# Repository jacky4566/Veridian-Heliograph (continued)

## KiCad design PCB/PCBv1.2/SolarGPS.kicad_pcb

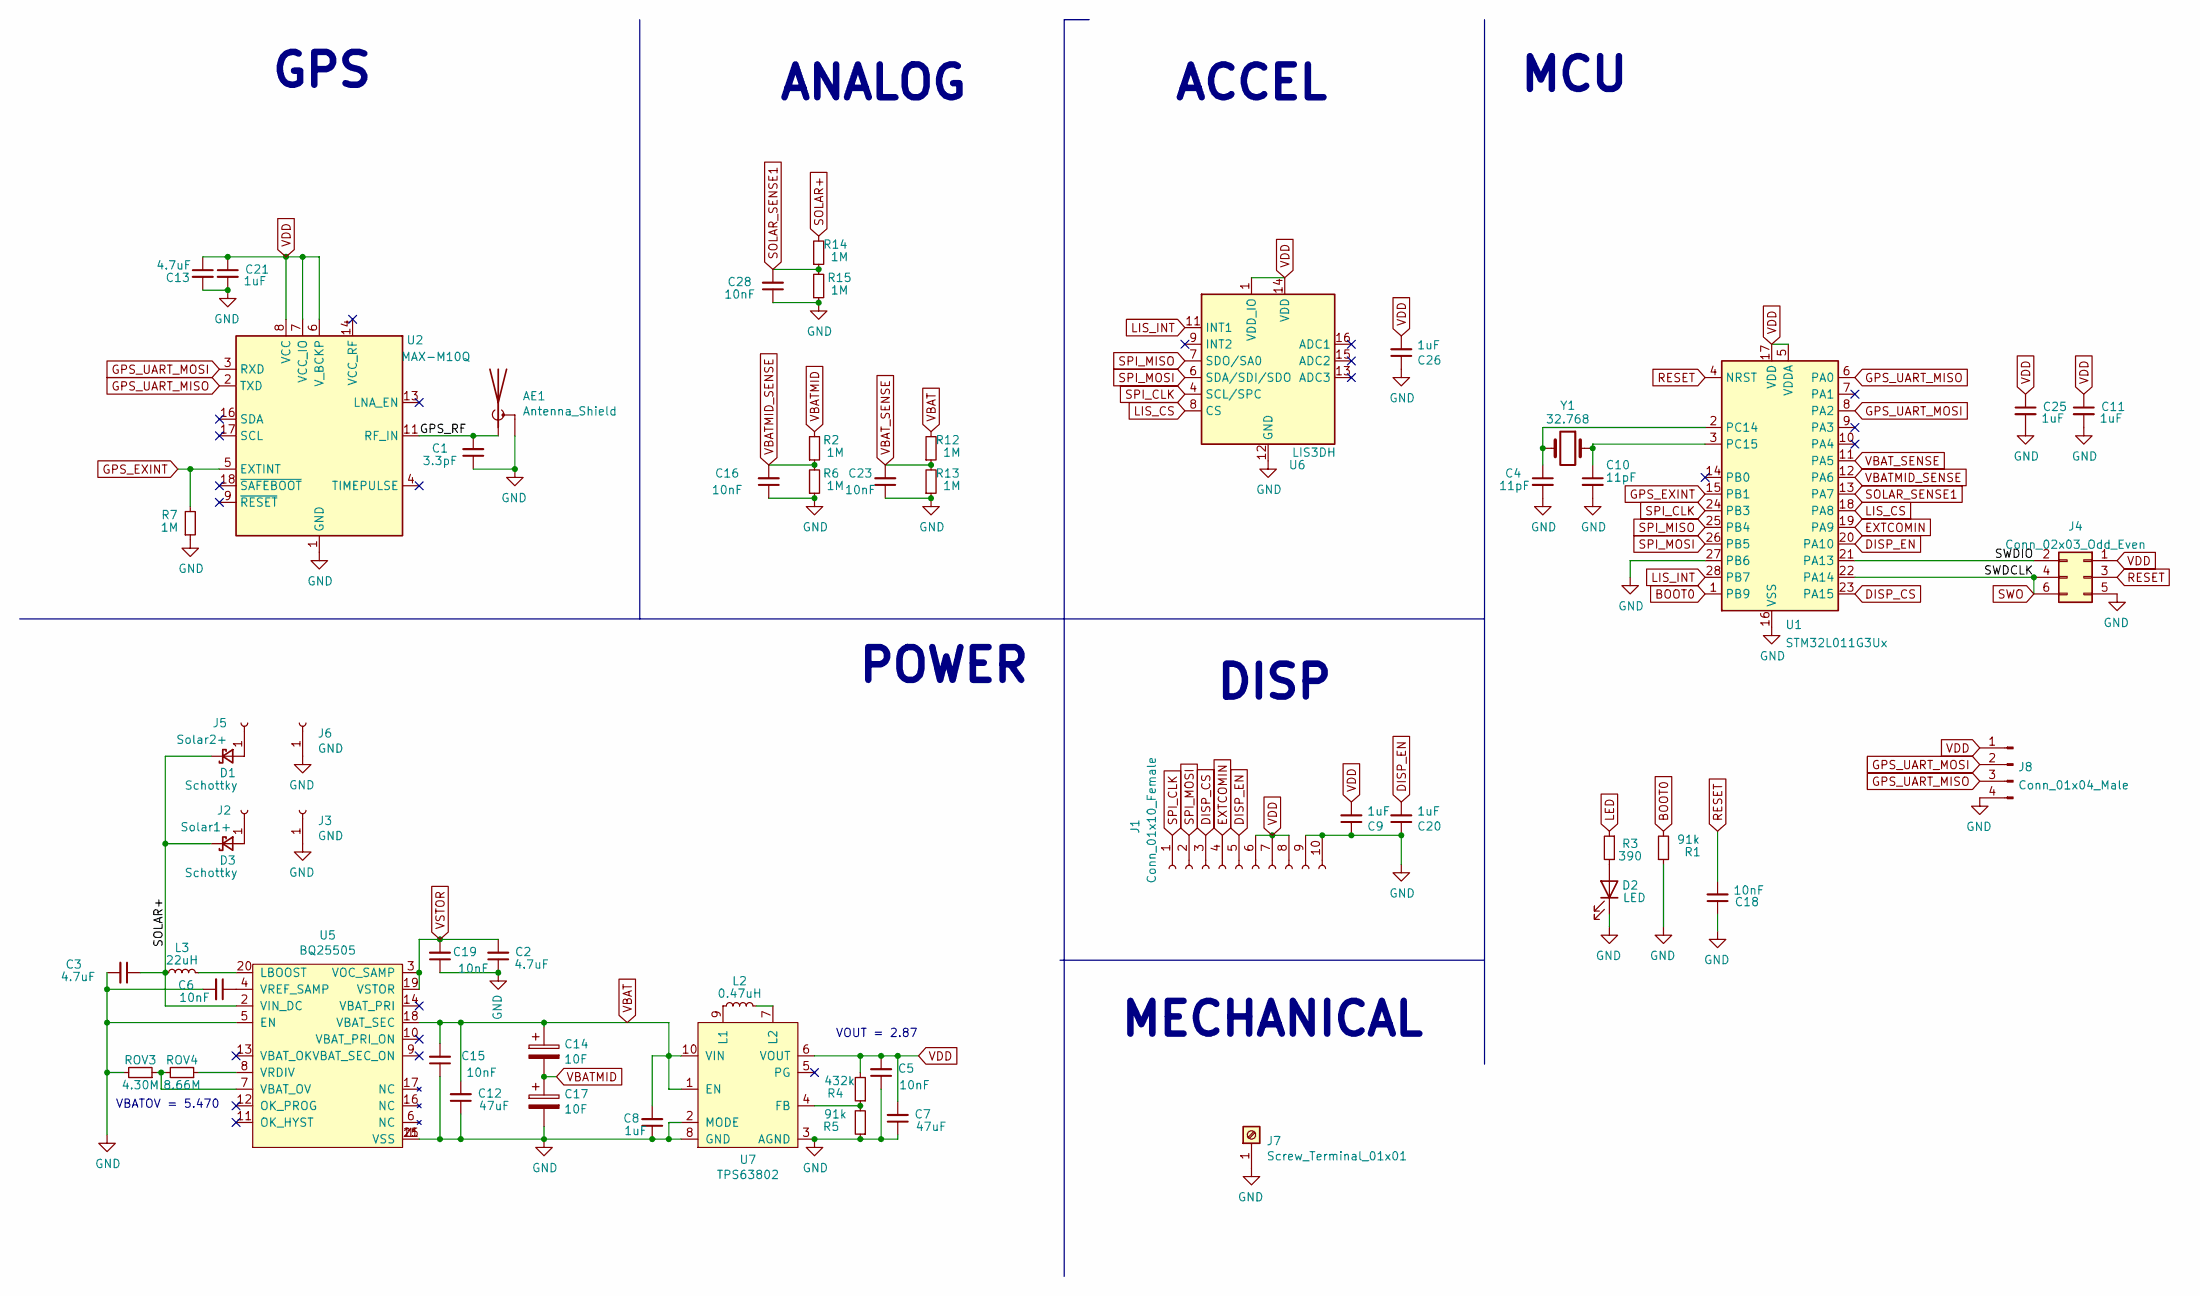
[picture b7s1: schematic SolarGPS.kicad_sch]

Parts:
AE1: Antenna_Shield; Pulse_W3011; Part W3011A
C1: 3.3pF; C_0402_1005Metric
C2, C3, C13: 4.7uF; C_0805_2012Metric
C4, C10: 11pF; C_0603_1608Metric
C5, C6, C15, C16, C18, C19, C23, C28: 10nF; C_0603_1608Metric
C7, C12: 47uF; C_1206_3216Metric
C8, C9, C11, C20, C21, C25, C26: 1uF; C_0603_1608Metric
C14, C17: 10F; SCCT20E106SRB; Part SCCT20E106SRB
D1, D3: Schottky; D_SOD-323_HandSoldering; Part B0530WS
D2: LED; D_0805_2012Metric; Part LS R976-NR-1
J1: Conn_01x10_Female; LS013B7DH03
J2: Solar1+; PinHeader_1x01_P2.54mm_Vertical
J3, J6: GND; PinHeader_1x01_P2.54mm_Vertical
J4: Conn_02x03_Odd_Even; Tag-Connect_TC2030-IDC-NL_2x03_P1.27mm_Vertical
J5: Solar2+; PinHeader_1x01_P2.54mm_Vertical
J7: Screw_Terminal_01x01; M4_RA_7792; Part 7792
J8: Conn_01x04_Male; PinSocket_1x04_P2.54mm_Vertical
L2: 0.47uH; L_0806_2016Metric; Part DFE201612E
L3: 22uH; L_1210_3225Metric; Part CBC3225T220MR
R1, R5: 91k; R_0603_1608Metric
R2, R6, R7, R12, R13, R14, R15: 1M; R_0603_1608Metric
R3: 390; R_0603_1608Metric
R4: 432k; R_0603_1608Metric
ROV3: 4.30M; R_0603_1608Metric
ROV4: 8.66M; R_0603_1608Metric
U1: STM32L011G3Ux; QFN-28_4x4mm_P0.5mm
U2: MAX-M10Q; ublox_MAX
U5: BQ25505; QFN-20-1EP_3.5x3.5mm_P0.5mm_EP2x2mm
U6: LIS3DH; LGA-16_3x3mm_P0.5mm_LayoutBorder3x5y
U7: TPS63802; VREG_TPS63802DLAR
Y1: 32.768; Crystal_SMD_3215-2Pin_3.2x1.5mm; Part SC32S-7PF20PPM

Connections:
/GPS_RF: AE1.1 (A), C1.2, U2.11 (RF_IN)
/SWDIO: J4.2, U1.21 (PA13)
BOOT0: R1.2, U1.1 (PB9)
DISP_CS: J1.3, U1.23 (PA15)
DISP_EN: C20.2, J1.5, U1.20 (PA10)
EXTCOMIN: J1.4, U1.19 (PA9)
GND: AE1.2 (Shield), C1.1, C2.1, C3.2, C4.2, C5.1, C6.2, C7.1, C8.1, C9.1, C10.2, C11.2, C12.1, C13.2, C15.1, C16.1, C17.2, C18.1, C19.1, C20.1, C21.2, C23.1, C25.2, C26.1, C28.1, D2.1 (K), J1.9, J1.10, J3.1, J4.5, J6.1, J7.1, J8.4, R1.1, R5.1, R6.1, R7.1, R13.1, R15.1, ROV3.2, U1.16 (VSS), U1.27 (PB6), U2.1 (GND), U2.10 (GND), U2.12 (GND), U5.1 (VSS), U5.5 (EN), U5.15 (VSS), U5.21 (VSS), U6.5 (GND), U6.10 (GND), U6.12 (GND), U7.2 (MODE), U7.3 (AGND), U7.8 (GND)
GPS_EXINT: R7.2, U1.15 (PB1), U2.5 (EXTINT)
GPS_UART_MISO: J8.3, U1.6 (PA0), U2.2 (TXD)
GPS_UART_MOSI: J8.2, U1.8 (PA2), U2.3 (RXD)
LED: R3.1
LIS_CS: U1.18 (PA8), U6.8 (CS)
LIS_INT: U1.28 (PB7), U6.11 (INT1)
unnamed: C4.1, U1.2 (PC14), Y1.2
unnamed: C6.1, U5.4 (VREF_SAMP)
unnamed: C10.1, U1.3 (PC15), Y1.1
unnamed: D1.2 (A), J5.1
unnamed: D2.2 (A), R3.2
unnamed: D3.2 (A), J2.1
unnamed: L2.1, U7.9 (L1)
unnamed: L2.2, U7.7 (L2)
unnamed: L3.2, U5.20 (LBOOST)
unnamed: R4.1, R5.2, U7.4 (FB)
unnamed: ROV3.1, ROV4.2, U5.7 (VBAT_OV)
unnamed: ROV4.1, U5.8 (VRDIV)
RESET: C18.2, J4.3, U1.4 (NRST)
SOLAR+: C3.1, D1.1 (K), D3.1 (K), L3.1, R14.2, U5.2 (VIN_DC)
SOLAR_SENSE1: C28.2, R14.1, R15.2, U1.13 (PA7)
SPI_CLK: J1.1, U1.24 (PB3), U6.4 (SCL/SPC)
SPI_MISO: U1.25 (PB4), U6.7 (SDO/SA0)
SPI_MOSI: J1.2, U1.26 (PB5), U6.6 (SDA/SDI/SDO)
SWO: J4.4, J4.6, U1.22 (PA14)
VBAT: C8.2, C12.2, C14.1, C15.2, R12.2, U5.18 (VBAT_SEC), U7.1 (EN), U7.10 (VIN)
VBATMID: C14.2, C17.1, R2.2
VBATMID_SENSE: C16.2, R2.1, R6.2, U1.12 (PA6)
VBAT_SENSE: C23.2, R12.1, R13.2, U1.11 (PA5)
VDD: C5.2, C7.2, C9.2, C11.1, C13.1, C21.1, C25.1, C26.2, J1.6, J1.7, J1.8, J4.1, J8.1, R4.2, U1.5 (VDDA), U1.17 (VDD), U2.6 (V_BCKP), U2.7 (VCC_IO), U2.8 (VCC), U6.1 (VDD_IO), U6.14 (VDD), U7.6 (VOUT)
VSTOR: C2.2, C19.2, U5.3 (VOC_SAMP), U5.19 (VSTOR)

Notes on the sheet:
VOUT = 2.87
GPS
MCU
ACCEL
DISP
POWER
VBATOV = 5.470
ANALOG
MECHANICAL

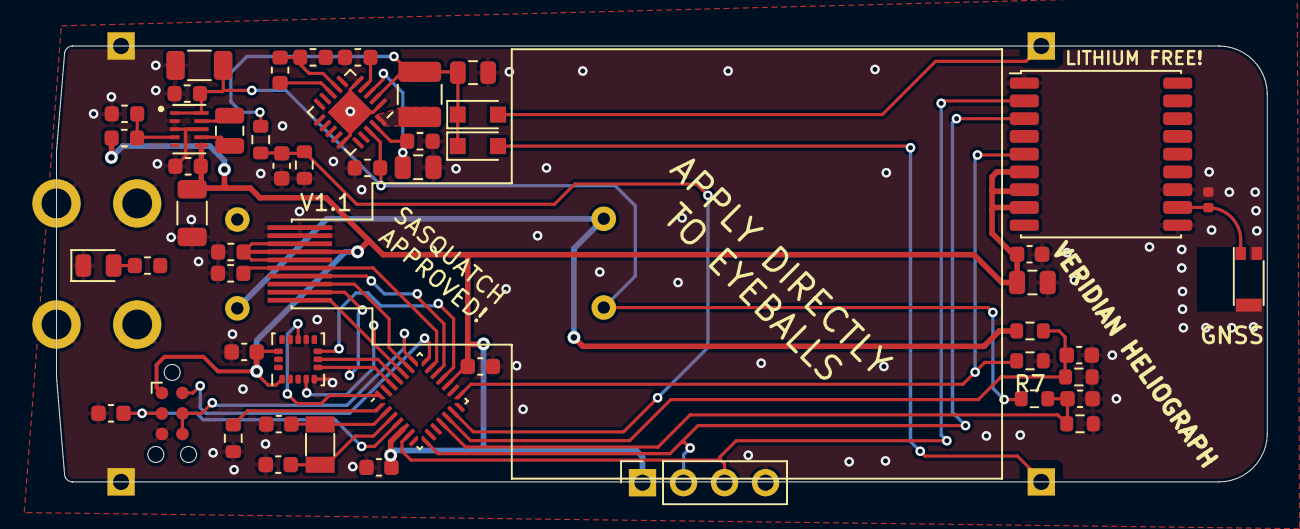
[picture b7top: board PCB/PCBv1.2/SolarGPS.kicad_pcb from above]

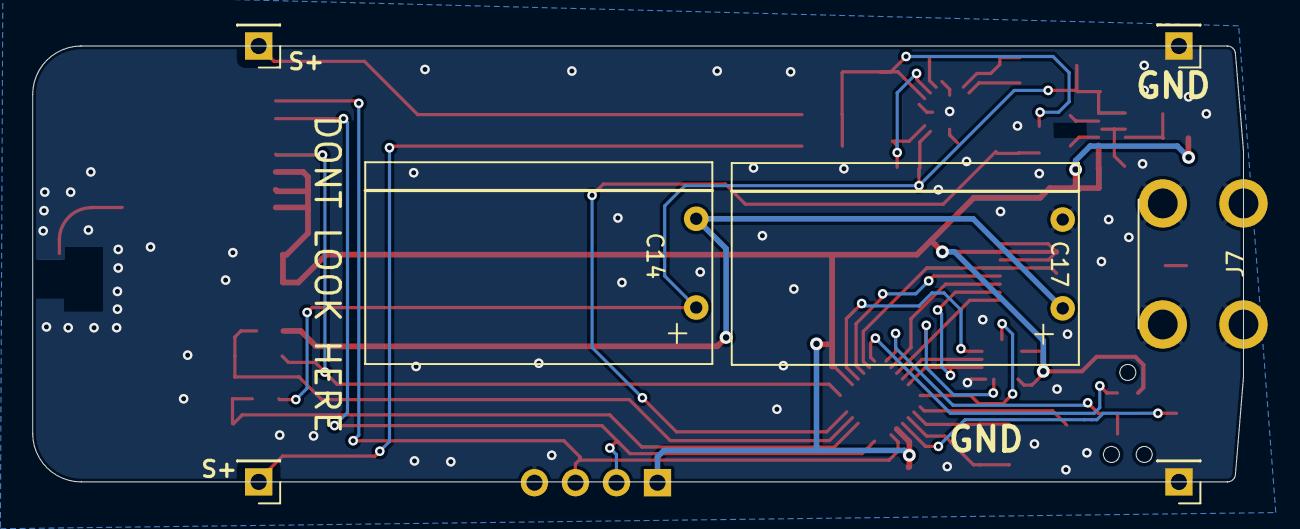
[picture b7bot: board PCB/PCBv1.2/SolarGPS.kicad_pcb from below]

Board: 2 copper layers, 75.0 x 27.0 mm, 58 parts (7 on the bottom side), 37 nets.

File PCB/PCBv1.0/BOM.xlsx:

Reference | Quantity | Value | Footprint | MANUFACTURER Part | Manufacture | Digikey Part | Cost CAD @100
U4 | 1 | STM32WB5MMGH6TR | Veridian-Library-KiCad:XCVR_STM32WB5MMGH6TR | STM32WB5MMGH6TR | STMicroelectronics | 497-STM32WB5MMGH6CT-ND | 15.1318
U2 | 1 | MAX-M10Q | RF_GPS:ublox_MAX | MAX-M10M-00B | U-Blox | 672-MAX-M10M-00BCT-ND | 12.2097
U5 | 1 | BQ25505 | Package_DFN_QFN:QFN-20-1EP_3.5x3.5mm_P0.5mm_EP2x2mm_ThermalVias | BQ25505RGRR | Texas Instruments | 296-37078-1-ND | 5.0499000000000001
C14 C17 | 2 | 10F | Veridian-Library-KiCad:SCCT20E106SRB | SCCT20E106SRB | KYOCERA AVX | 478-11288-ND | 2.9862000000000002
U6 | 1 | LIS3DH | Package_LGA:LGA-16_3x3mm_P0.5mm_LayoutBorder3x5y | LIS3DHTR | STMicroelectronics | 497-10613-1-ND | 2.0329999999999999
U7 | 1 | TPS63802 | Margo_Lib:VREG_TPS63802DLAR | TPS63802DLAR | Texas Instruments | 296-TPS63802DLARCT-ND | 1.9172
AE1 | 1 | Antenna_Shield |  | W3011A | PulseLarsen Antennas | 553-1671-1-ND | 1.6272
J1 | 1 | Conn_01x10_Female | Margo_Lib:AYF531035 | AYF531035A | Panasonic Electric Works | 255-5667-ND | 1.0860000000000001
J4 | 1 | Conn_02x05_Odd_Even |  | PM20C05VBDN | METZ CONNECT USA Inc. | 1849-1015-ND | 0.63029999999999997
J7 | 1 | Screw_Terminal_01x01 | Veridian-Library-KiCad:Right Angle Screw Terminal M3M4 | 7781 | Keystone Electronics | 36-7781-ND | 0.5131
C7 C12 | 2 | 100uF | Capacitor_SMD:C_1206_3216Metric | GRM31CD80J107MEA8K | Murata Electronics | 490-GRM31CD80J107MEA8KCT-ND | 0.35210000000000002
L2 | 1 | 0.47uH | Inductor_SMD:L_0806_2016Metric | DFE201612E | Murata Electronics | 490-16593-1-ND | 0.31069999999999998
L3 | 1 | 22uH | Inductor_SMD:L_1008_2520Metric | CBC3225T220MR | Taiyo Yuden | 587-1626-1-ND | 0.27110000000000001
D1 D3 | 2 | Schottky | Diode_SMD:D_SOD-323_HandSoldering | B0530WS | Taiwan Semiconductor Corporation | B0530WSRRGCT-ND | 0.22270000000000001
C2 C3 | 2 | 4.7uF | Capacitor_SMD:C_0805_2012Metric | GRM188Z71A475ME15D | Murata Electronics | 490-GRM188Z71A475ME15DCT-ND | 0.18279999999999999
D4 | 1 | 5.1V | Diode_SMD:D_SOD-523 | BZT52C5V1T-TP | Micro Commercial Co | BZT52C5V1T-TPMSCT-ND | 0.17299999999999999
D2 | 1 | LED | Diode_SMD:D_0805_2012Metric | LS R976-NR-1 | OSRAM Opto Semiconductors Inc. | 475-1278-1-ND | 0.1069
C5 C6 C15 C16 C18 C19 C23 C28 | 8 | 10nF | Capacitor_SMD:C_0603_1608Metric | GRM1885C1H103JA01J | Murata Electronics | 490-GRM1885C1H103JA01JCT-ND | 9.4100000000000003E-2
C1, C10, C11, C13 | 4 | 3.3pF | Capacitor_SMD:C_0402_1005Metric | CBR04C339C5GAC | KEMET | 399-6165-1-ND | 0.06
C4, C8, C9, C20, C21, C25, C26 | 7 | 1uF | Capacitor_SMD:C_0603_1608Metric | GRM188R61A105KA61J | Murata Electronics | 490-6408-1-ND | 3.8899999999999997E-2
R1 R2 R6 R12 R13 R14 R15 | 7 | 1M | Resistor_SMD:R_0603_1608Metric | RC0603FR-071ML | YAGEO | 311-1.00MHRCT-ND | 1.43E-2
R4 | 1 | 412k | Resistor_SMD:R_0603_1608Metric | RC0603FR-07412KL | YAGEO | 311-412KHRCT-ND | 1.43E-2
R5 | 1 | 91k | Resistor_SMD:R_0603_1608Metric | RC0603FR-0791KL | YAGEO | 311-91.0KHRCT-ND | 1.43E-2
ROV3 | 1 | 4.32M | Resistor_SMD:R_0603_1608Metric | RC0603FR-074M3L | YAGEO | 13-RC0603FR-074M3LCT-ND | 1.43E-2
ROV4 | 1 | 8.66M | Resistor_SMD:R_0603_1608Metric | RC0603FR-078M66L | YAGEO | RC0603FR-078M66L-ND | 1.43E-2
R3 | 1 | 390 | Resistor_SMD:R_0603_1608Metric | RC0603JR-07390RL | YAGEO | 311-390GRCT-ND | 1.18E-2
J2 | 1 | Solar1+ |  | DNF
J3 J6 | 2 | GND |  | DNF
J5 | 1 | Solar2+ |  | DNF
DISP1 | 1 |  |  | LS013B7DH03 | Sharp Microelectronics | 425-2903-ND | 11.003
SOLAR | 2 |  |  | SM141K09L | ANYSOLAR Ltd | SM141K09L-ND | 8.5571000000000002
PCB | 1 |  |  |  |  |  | 1
Epoxy | 1 |  |  |  |  |  | 3
 |  |  |  |  |  |  | 82.0989

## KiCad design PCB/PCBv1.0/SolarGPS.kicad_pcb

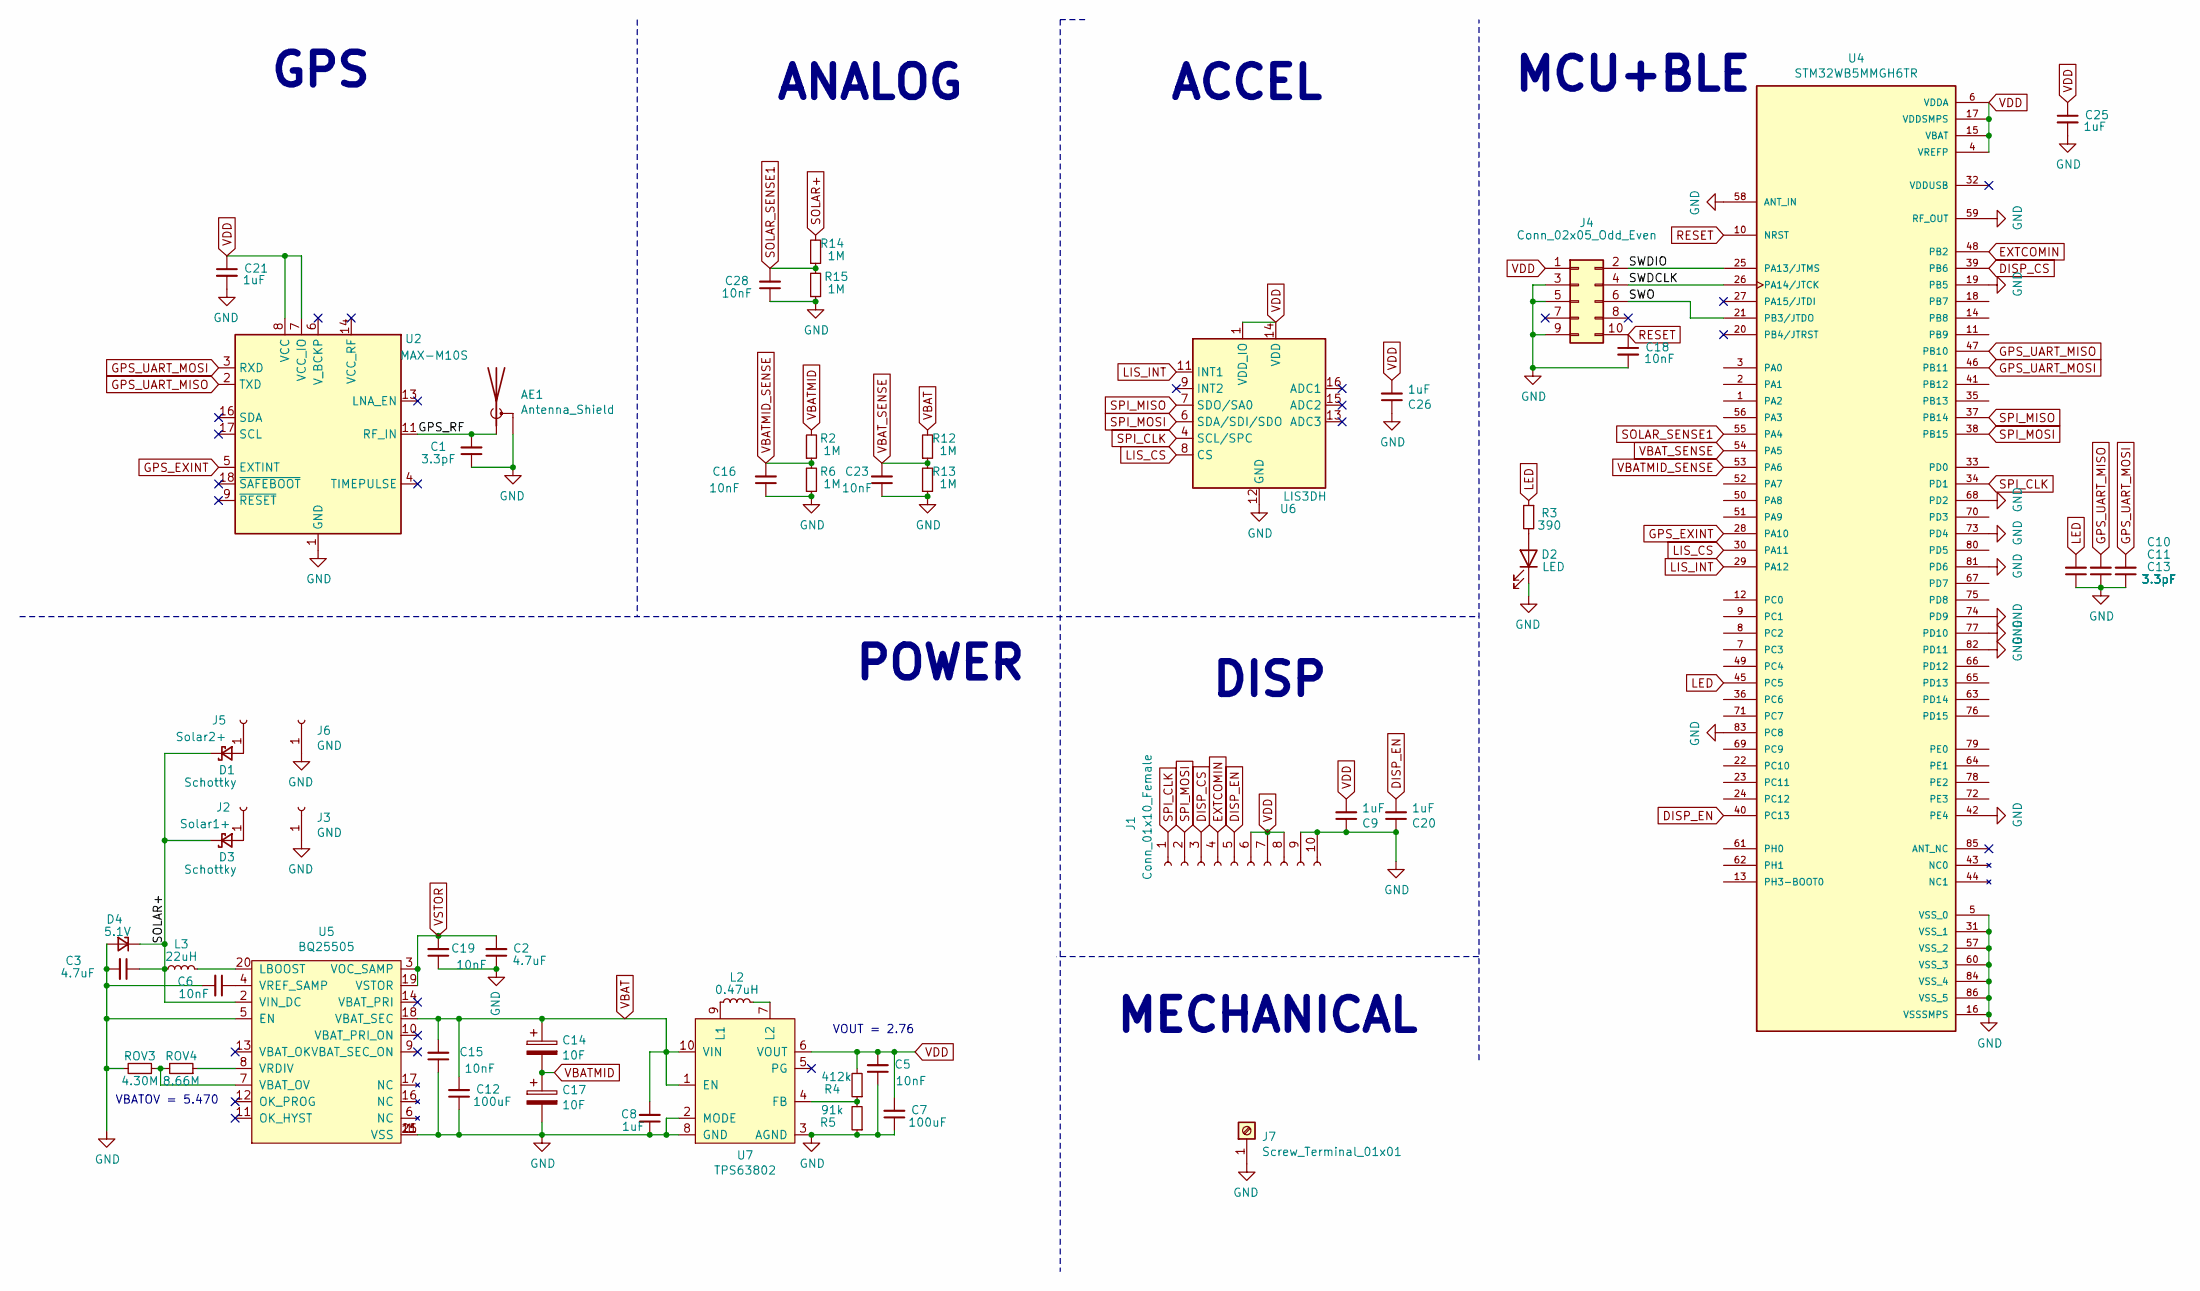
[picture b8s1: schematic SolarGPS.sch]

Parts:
AE1: Antenna_Shield; Pulse_W3011; Part W3011A
C1, C10, C11, C13: 3.3pF; C_0402_1005Metric
C2, C3: 4.7uF; C_0805_2012Metric
C5, C6, C15, C16, C18, C19, C23, C28: 10nF; C_0603_1608Metric
C7, C12: 100uF; C_1206_3216Metric
C8, C9, C20, C21, C25, C26: 1uF; C_0603_1608Metric
C14, C17: 10F; SCCT20E106SRB; Part SCCT20E106SRB
D1, D3: Schottky; D_SOD-323_HandSoldering; Part B0530WS-TP
D2: LED; D_0805_2012Metric; Part LS R976-NR-1
D4: 5.1V; D_SOD-523; Part BZT52C5V1T-TP
J1: Conn_01x10_Female; AYF531035
J2: Solar1+; PinHeader_1x01_P2.54mm_Vertical
J3, J6: GND; PinHeader_1x01_P2.54mm_Vertical
J4: Conn_02x05_Odd_Even; PinHeader_2x05_P2.00mm_Vertical_SMD; Part PM20C05VBDN
J5: Solar2+; PinHeader_1x01_P2.54mm_Vertical
J7: Screw_Terminal_01x01; Right Angle Screw Terminal M3M4; Part 7781
L2: 0.47uH; L_0806_2016Metric; Part CIGT201208EHR47MNE
L3: 22uH; L_1210_3225Metric; Part CBC3225T220MR
R2, R6, R12, R13, R14, R15: 1M; R_0603_1608Metric
R3: 390; R_0603_1608Metric
R4: 412k; R_0603_1608Metric
R5: 91k; R_0603_1608Metric
ROV3: 4.30M; R_0603_1608Metric
ROV4: 8.66M; R_0603_1608Metric
U2: MAX-M10S; ublox_MAX
U4: STM32WB5MMGH6TR; XCVR_STM32WB5MMGH6TR; PARTREV Rev 1
U5: BQ25505; QFN-20-1EP_3.5x3.5mm_P0.5mm_EP2x2mm_ThermalVias
U6: LIS3DH; LGA-16_3x3mm_P0.5mm_LayoutBorder3x5y
U7: TPS63802; VREG_TPS63802DLAR

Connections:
/GPS_RF: AE1.1 (A), C1.2, U2.11 (RF_IN)
/SWDCLK: J4.4, U4.26 (PA14/JTCK)
/SWDIO: J4.2, U4.25 (PA13/JTMS)
/SWO: J4.6, U4.21 (PB3/JTDO)
DISP_CS: J1.3, U4.39 (PB6)
DISP_EN: C20.2, J1.5, U4.40 (PC13)
EXTCOMIN: J1.4, U4.48 (PB2)
GND: AE1.2 (Shield), C1.1, C2.1, C3.2, C5.1, C6.2, C7.1, C8.1, C9.1, C10.1, C11.1, C12.1, C13.1, C15.1, C16.1, C17.2, C18.2, C19.1, C20.1, C21.2, C23.1, C25.2, C26.1, C28.1, D2.1 (K), D4.2 (A), J1.9, J1.10, J3.1, J4.3, J4.5, J4.9, J6.1, J7.1, R5.1, R6.1, R13.1, R15.1, ROV3.2, U2.1 (GND), U2.10 (GND), U2.12 (GND), U4.5 (VSS_0), U4.16 (VSSSMPS), U4.19 (PB5), U4.31 (VSS_1), U4.42 (PE4), U4.57 (VSS_2), U4.58 (ANT_IN), U4.59 (RF_OUT), U4.60 (VSS_3), U4.68 (PD2), U4.73 (PD4), U4.74 (PD9), U4.77 (PD10), U4.81 (PD6), U4.82 (PD11), U4.83 (PC8), U4.84 (VSS_4), U4.86 (VSS_5), U5.1 (VSS), U5.5 (EN), U5.15 (VSS), U5.21 (VSS), U6.5 (GND), U6.10 (GND), U6.12 (GND), U7.2 (MODE), U7.3 (AGND), U7.8 (GND)
GPS_EXINT: U2.5 (EXTINT), U4.28 (PA10)
GPS_UART_MISO: C11.2, U2.2 (TXD), U4.47 (PB10)
GPS_UART_MOSI: C13.2, U2.3 (RXD), U4.46 (PB11)
LED: C10.2, R3.1, U4.45 (PC5)
LIS_CS: U4.30 (PA11), U6.8 (CS)
LIS_INT: U4.29 (PA12), U6.11 (INT1)
unnamed: C6.1, U5.4 (VREF_SAMP)
unnamed: D1.2 (A), J5.1
unnamed: D2.2 (A), R3.2
unnamed: D3.2 (A), J2.1
unnamed: L2.1, U7.9 (L1)
unnamed: L2.2, U7.7 (L2)
unnamed: L3.2, U5.20 (LBOOST)
unnamed: R4.1, R5.2, U7.4 (FB)
unnamed: ROV3.1, ROV4.2, U5.7 (VBAT_OV)
unnamed: ROV4.1, U5.8 (VRDIV)
RESET: C18.1, J4.10, U4.10 (NRST)
SOLAR+: C3.1, D1.1 (K), D3.1 (K), D4.1 (K), L3.1, R14.2, U5.2 (VIN_DC)
SOLAR_SENSE1: C28.2, R14.1, R15.2, U4.55 (PA4)
SPI_CLK: J1.1, U4.34 (PD1), U6.4 (SCL/SPC)
SPI_MISO: U4.37 (PB14), U6.7 (SDO/SA0)
SPI_MOSI: J1.2, U4.38 (PB15), U6.6 (SDA/SDI/SDO)
VBAT: C8.2, C12.2, C14.1, C15.2, R12.2, U5.18 (VBAT_SEC), U7.1 (EN), U7.10 (VIN)
VBATMID: C14.2, C17.1, R2.2
VBATMID_SENSE: C16.2, R2.1, R6.2, U4.53 (PA6)
VBAT_SENSE: C23.2, R12.1, R13.2, U4.54 (PA5)
VDD: C5.2, C7.2, C9.2, C21.1, C25.1, C26.2, J1.6, J1.7, J1.8, J4.1, R4.2, U2.7 (VCC_IO), U2.8 (VCC), U4.4 (VREFP), U4.6 (VDDA), U4.15 (VBAT), U4.17 (VDDSMPS), U6.1 (VDD_IO), U6.14 (VDD), U7.6 (VOUT)
VSTOR: C2.2, C19.2, U5.3 (VOC_SAMP), U5.19 (VSTOR)

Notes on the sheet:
VBATOV = 5.470
VOUT = 2.76
MCU+BLE
POWER
ACCEL
ANALOG
GPS
DISP
MECHANICAL

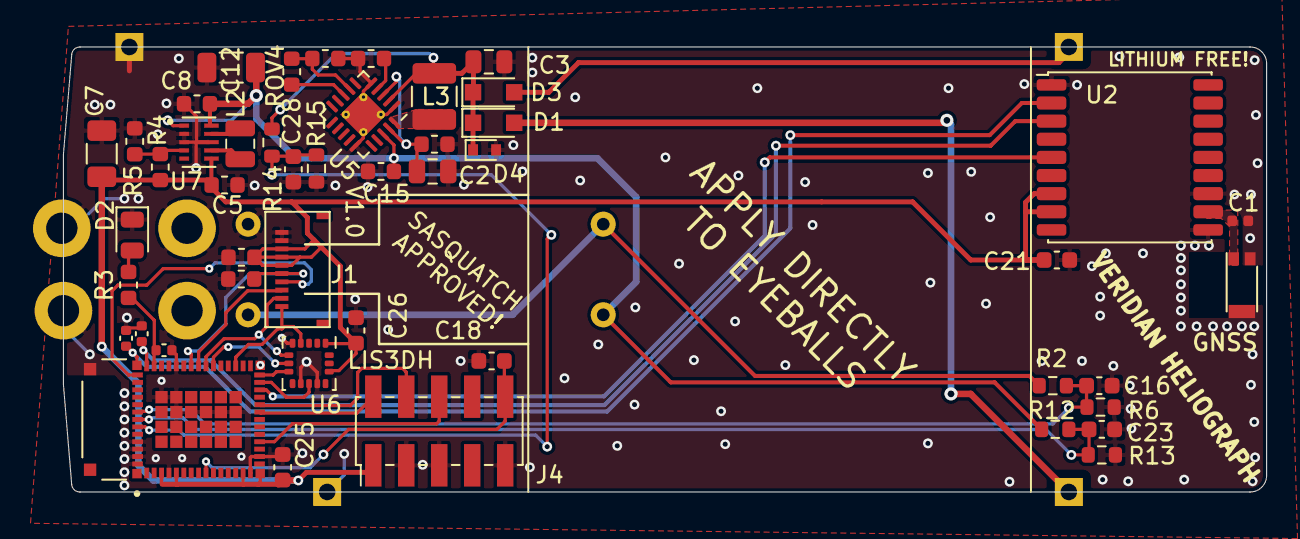
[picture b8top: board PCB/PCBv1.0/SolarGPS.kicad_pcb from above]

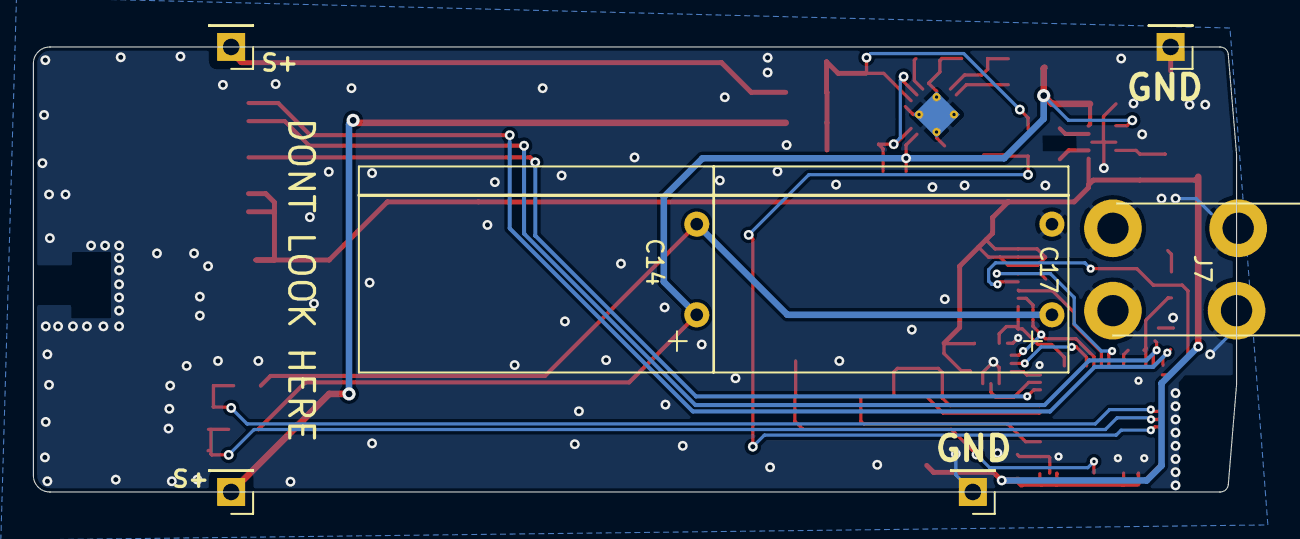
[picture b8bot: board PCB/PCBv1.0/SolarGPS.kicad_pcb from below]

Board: 2 copper layers, 73.0 x 27.0 mm, 54 parts (7 on the bottom side), 36 nets.

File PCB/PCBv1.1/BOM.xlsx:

Reference | Quantity | Value | Footprint | MANUFACTURER Part | Manufacture | Digikey Part | Cost CAD @100
U4 | 1 | STM32WB5MMGH6TR | Veridian-Library-KiCad:XCVR_STM32WB5MMGH6TR | STM32WB5MMGH6TR | STMicroelectronics | 497-STM32WB5MMGH6CT-ND | 15.1318
U2 | 1 | MAX-M10Q | RF_GPS:ublox_MAX | MAX-M10M-00B | U-Blox | 672-MAX-M10M-00BCT-ND | 12.2097
U5 | 1 | BQ25505 | Package_DFN_QFN:QFN-20-1EP_3.5x3.5mm_P0.5mm_EP2x2mm_ThermalVias | BQ25505RGRR | Texas Instruments | 296-37078-1-ND | 5.0499000000000001
C14 C17 | 2 | 10F | Veridian-Library-KiCad:SCCT20E106SRB | SCCT20E106SRB | KYOCERA AVX | 478-11288-ND | 2.9862000000000002
U6 | 1 | LIS3DH | Package_LGA:LGA-16_3x3mm_P0.5mm_LayoutBorder3x5y | LIS3DHTR | STMicroelectronics | 497-10613-1-ND | 2.0329999999999999
U7 | 1 | TPS63802 | Margo_Lib:VREG_TPS63802DLAR | TPS63802DLAR | Texas Instruments | 296-TPS63802DLARCT-ND | 1.9172
AE1 | 1 | Antenna_Shield |  | W3011A | PulseLarsen Antennas | 553-1671-1-ND | 1.6272
J1 | 1 | Conn_01x10_Female | Margo_Lib:AYF531035 | AYF531035A | Panasonic Electric Works | 255-5667-ND | 1.0860000000000001
J4 | 1 | Conn_02x05_Odd_Even |  | PM20C05VBDN | METZ CONNECT USA Inc. | 1849-1015-ND | 0.63029999999999997
J7 | 1 | Screw_Terminal_01x01 | Veridian-Library-KiCad:Right Angle Screw Terminal M3M4 | 7781 | Keystone Electronics | 36-7781-ND | 0.5131
C7 C12 | 2 | 100uF | Capacitor_SMD:C_1206_3216Metric | GRM31CD80J107MEA8K | Murata Electronics | 490-GRM31CD80J107MEA8KCT-ND | 0.35210000000000002
L2 | 1 | 0.47uH | Inductor_SMD:L_0806_2016Metric | DFE201612E | Murata Electronics | 490-16593-1-ND | 0.31069999999999998
L3 | 1 | 22uH | Inductor_SMD:L_1008_2520Metric | CBC3225T220MR | Taiyo Yuden | 587-1626-1-ND | 0.27110000000000001
D1 D3 | 2 | Schottky | Diode_SMD:D_SOD-323_HandSoldering | B0530WS | Taiwan Semiconductor Corporation | B0530WSRRGCT-ND | 0.22270000000000001
C2 C3 | 2 | 4.7uF | Capacitor_SMD:C_0805_2012Metric | GRM188Z71A475ME15D | Murata Electronics | 490-GRM188Z71A475ME15DCT-ND | 0.18279999999999999
D4 | 1 | 5.1V | Diode_SMD:D_SOD-523 | BZT52C5V1T-TP | Micro Commercial Co | BZT52C5V1T-TPMSCT-ND | 0.17299999999999999
D2 | 1 | LED | Diode_SMD:D_0805_2012Metric | LS R976-NR-1 | OSRAM Opto Semiconductors Inc. | 475-1278-1-ND | 0.1069
C5 C6 C15 C16 C18 C19 C23 C28 | 8 | 10nF | Capacitor_SMD:C_0603_1608Metric | GRM1885C1H103JA01J | Murata Electronics | 490-GRM1885C1H103JA01JCT-ND | 9.4100000000000003E-2
C1, C10, C11, C13 | 4 | 3.3pF | Capacitor_SMD:C_0402_1005Metric | CBR04C339C5GAC | KEMET | 399-6165-1-ND | 0.06
C8, C9, C20, C21, C25, C26 | 6 | 1uF | Capacitor_SMD:C_0603_1608Metric | GRM188R61A105KA61J | Murata Electronics | 490-6408-1-ND | 3.8899999999999997E-2
R2 R6 R12 R13 R14 R15 | 6 | 1M | Resistor_SMD:R_0603_1608Metric | RC0603FR-071ML | YAGEO | 311-1.00MHRCT-ND | 1.43E-2
R4 | 1 | 412k | Resistor_SMD:R_0603_1608Metric | RC0603FR-07412KL | YAGEO | 311-412KHRCT-ND | 1.43E-2
R5 | 1 | 91k | Resistor_SMD:R_0603_1608Metric | RC0603FR-0791KL | YAGEO | 311-91.0KHRCT-ND | 1.43E-2
ROV3 | 1 | 4.32M | Resistor_SMD:R_0603_1608Metric | RC0603FR-074M3L | YAGEO | 13-RC0603FR-074M3LCT-ND | 1.43E-2
ROV4 | 1 | 8.66M | Resistor_SMD:R_0603_1608Metric | RC0603FR-078M66L | YAGEO | RC0603FR-078M66L-ND | 1.43E-2
R3 | 1 | 390 | Resistor_SMD:R_0603_1608Metric | RC0603JR-07390RL | YAGEO | 311-390GRCT-ND | 1.18E-2
J2 | 1 | Solar1+ |  | DNF
J3 J6 | 2 | GND |  | DNF
J5 | 1 | Solar2+ |  | DNF
DISP1 | 1 |  |  | LS013B7DH03 | Sharp Microelectronics | 425-2903-ND | 11.003
SOLAR | 2 |  |  | SM141K09L | ANYSOLAR Ltd | SM141K09L-ND | 8.5571000000000002
PCB | 1 |  |  |  |  |  | 1
Epoxy | 1 |  |  |  |  |  | 3
 |  |  |  |  |  |  | 82.045699999999997

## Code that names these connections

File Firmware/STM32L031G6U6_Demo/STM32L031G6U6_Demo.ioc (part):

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Mcu.Name=STM32L031G(4-6)Ux
Mcu.Package=UFQFPN28
Mcu.UserName=STM32L031G6Ux
PA0-CK_IN.GPIOParameters=GPIO_Label
PA0-CK_IN.GPIO_Label=ADC_SOLAR
PA0-CK_IN.Mode=IN0
PA0-CK_IN.Signal=ADC_IN0
PA1.GPIOParameters=GPIO_Label
PA1.GPIO_Label=GPS_EXT
PA1.Signal=GPIO_Output
PA10.GPIOParameters=GPIO_Label
PA10.GPIO_Label=DISPCS
PA10.Signal=GPIO_Output
PA14.Mode=WaveformGeneration
PA14.Signal=LPTIM1_OUT
PA2.Mode=Asynchronous
PA2.Signal=LPUART1_TX
PA3.Mode=Asynchronous
PA3.Signal=LPUART1_RX
PA4.GPIOParameters=GPIO_Label
PA4.GPIO_Label=LIS_CS
PA4.Signal=GPIO_Output
PA5.Mode=Full_Duplex_Master
PA5.Signal=SPI1_SCK
PA6.Mode=Full_Duplex_Master
PA6.Signal=SPI1_MISO
PA7.Mode=Full_Duplex_Master
PA7.Signal=SPI1_MOSI
PA8.GPIOParameters=GPIO_Label
PA8.GPIO_Label=DISPEN
PA8.Signal=GPIO_Output
PB0.GPIOParameters=GPIO_Label
PB0.GPIO_Label=LIS_INT
PB0.Signal=GPXTI0
PB1.GPIOParameters=GPIO_Label,GPIO_ModeDefaultEXTI
PB1.GPIO_Label=VBAT_OK
PB1.GPIO_ModeDefaultEXTI=GPIO_MODE_IT_RISING_FALLING
PB1.Signal=GPXTI1
PC14-OSC32_IN.Mode=LSE-External-Oscillator
PC14-OSC32_IN.Signal=RCC_OSC32_IN
PC15-OSC32_OUT.Mode=LSE-External-Oscillator
PC15-OSC32_OUT.Signal=RCC_OSC32_OUT
RCC.HSE_VALUE=8000000
RCC.SYSCLKFreq_VALUE=16000000
RCC.SYSCLKSource=RCC_SYSCLKSOURCE_HSI
board=custom

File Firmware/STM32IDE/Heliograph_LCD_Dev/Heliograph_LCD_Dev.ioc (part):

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Mcu.Name=STM32L031G(4-6)Ux
Mcu.Package=UFQFPN28
Mcu.UserName=STM32L031G6Ux
PA1.GPIOParameters=GPIO_Label
PA1.GPIO_Label=GNSS_EXT
PA1.Signal=GPIO_Output
PA10.GPIOParameters=GPIO_Label
PA10.GPIO_Label=DISP_CS
PA10.Signal=GPIO_Output
PA13.Mode=Serial_Wire
PA13.Signal=SYS_SWDIO
PA14.Mode=Serial_Wire
PA14.Signal=SYS_SWCLK
PA2.Mode=Asynchronous
PA2.Signal=LPUART1_TX
PA3.Mode=Asynchronous
PA3.Signal=LPUART1_RX
PA4.GPIOParameters=GPIO_Label
PA4.GPIO_Label=Debug
PA4.Signal=GPIO_Output
PA5.Mode=Full_Duplex_Master
PA5.Signal=SPI1_SCK
PA6.Mode=Full_Duplex_Master
PA6.Signal=SPI1_MISO
PA7.Mode=Full_Duplex_Master
PA7.Signal=SPI1_MOSI
PA8.GPIOParameters=GPIO_Label
PA8.GPIO_Label=DISP_EN
PA8.Signal=GPIO_Output
PB1.GPIOParameters=GPIO_Label,GPIO_ModeDefaultEXTI
PB1.GPIO_Label=VBAT_OK_PIN
PB1.GPIO_ModeDefaultEXTI=GPIO_MODE_IT_RISING_FALLING
PB1.Signal=GPXTI1
PC14-OSC32_IN.Mode=LSE-External-Oscillator
PC14-OSC32_IN.Signal=RCC_OSC32_IN
PC15-OSC32_OUT.Mode=LSE-External-Oscillator
PC15-OSC32_OUT.Signal=RCC_OSC32_OUT
RCC.HSE_VALUE=8000000
RCC.SYSCLKFreq_VALUE=16000000
RCC.SYSCLKSource=RCC_SYSCLKSOURCE_HSI
board=custom

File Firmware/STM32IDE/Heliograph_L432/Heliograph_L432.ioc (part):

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Mcu.Name=STM32L432K(B-C)Ux
Mcu.Package=UFQFPN32
Mcu.UserName=STM32L432KCUx
PA1.Signal=ADCx_IN6
PA10.GPIOParameters=GPIO_Label
PA10.GPIO_Label=DISP_EN
PA10.Signal=GPIO_Output
PA13\ (JTMS-SWDIO).Mode=Serial_Wire
PA13\ (JTMS-SWDIO).Signal=SYS_JTMS-SWDIO
PA14\ (JTCK-SWCLK).Mode=Serial_Wire
PA14\ (JTCK-SWCLK).Signal=SYS_JTCK-SWCLK
PA2.Mode=Asynchronous
PA2.Signal=LPUART1_TX
PA3.Mode=Asynchronous
PA3.Signal=LPUART1_RX
PA4.GPIOParameters=PinState,GPIO_Label
PA4.GPIO_Label=GNSS_EXT
PA4.PinState=GPIO_PIN_RESET
PA4.Signal=GPIO_Output
PA5.Mode=Full_Duplex_Master
PA5.Signal=SPI1_SCK
PA6.Mode=Full_Duplex_Master
PA6.Signal=SPI1_MISO
PA7.Mode=Full_Duplex_Master
PA7.Signal=SPI1_MOSI
PA8.GPIOParameters=PinState,GPIO_PuPd,GPIO_Label,GPIO_ModeDefaultOutputPP
PA8.GPIO_Label=SolarEN
PA8.GPIO_ModeDefaultOutputPP=GPIO_MODE_OUTPUT_OD
PA8.GPIO_PuPd=GPIO_NOPULL
PA8.PinState=GPIO_PIN_SET
PA8.Signal=GPIO_Output
PA9.GPIOParameters=GPIO_Label
PA9.GPIO_Label=DISP_CS
PA9.Signal=GPIO_Output
PC14-OSC32_IN\ (PC14).Mode=LSE-External-Oscillator
PC14-OSC32_IN\ (PC14).Signal=RCC_OSC32_IN
PC15-OSC32_OUT\ (PC15).Mode=LSE-External-Oscillator
PC15-OSC32_OUT\ (PC15).Signal=RCC_OSC32_OUT
RCC.HSE_VALUE=8000000
RCC.SYSCLKFreq_VALUE=16000000
board=custom

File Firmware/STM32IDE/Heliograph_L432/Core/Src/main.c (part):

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
  LL_AHB2_GRP1_EnableClock(LL_AHB2_GRP1_PERIPH_GPIOA);
  /**LPUART1 GPIO Configuration
  PA2   ------> LPUART1_TX
  PA3   ------> LPUART1_RX
  */
  GPIO_InitStruct.Pin = LL_GPIO_PIN_2|LL_GPIO_PIN_3;
  GPIO_InitStruct.Mode = LL_GPIO_MODE_ALTERNATE;
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  __HAL_RCC_GPIOH_CLK_ENABLE();

  /*Configure GPIO pin Output Level */
  HAL_GPIO_WritePin(GPIOA, GNSS_EXT_Pin|DISP_CS_Pin|DISP_EN_Pin, GPIO_PIN_RESET);

  /*Configure GPIO pin Output Level */
  HAL_GPIO_WritePin(SolarEN_GPIO_Port, SolarEN_Pin, GPIO_PIN_SET);

  /*Configure GPIO pins : PA0 PA11 PA12 PA15 */
  GPIO_InitStruct.Pin = GPIO_PIN_0|GPIO_PIN_11|GPIO_PIN_12|GPIO_PIN_15;
  GPIO_InitStruct.Mode = GPIO_MODE_ANALOG;
  GPIO_InitStruct.Pull = GPIO_NOPULL;
  HAL_GPIO_Init(GPIOA, &GPIO_InitStruct);

  /*Configure GPIO pins : GNSS_EXT_Pin DISP_CS_Pin DISP_EN_Pin */
  GPIO_InitStruct.Pin = GNSS_EXT_Pin|DISP_CS_Pin|DISP_EN_Pin;
  GPIO_InitStruct.Mode = GPIO_MODE_OUTPUT_PP;
  GPIO_InitStruct.Pull = GPIO_NOPULL;
  GPIO_InitStruct.Speed = GPIO_SPEED_FREQ_LOW;
  HAL_GPIO_Init(GPIOA, &GPIO_InitStruct);

  /*Configure GPIO pins : PB0 PB1 PB3 PB4
                           PB5 PB6 PB7 */
  GPIO_InitStruct.Pin = GPIO_PIN_0|GPIO_PIN_1|GPIO_PIN_3|GPIO_PIN_4
                          |GPIO_PIN_5|GPIO_PIN_6|GPIO_PIN_7;
  GPIO_InitStruct.Mode = GPIO_MODE_ANALOG;
  GPIO_InitStruct.Pull = GPIO_NOPULL;
  HAL_GPIO_Init(GPIOB, &GPIO_InitStruct);

  /*Configure GPIO pin : SolarEN_Pin */
  GPIO_InitStruct.Pin = SolarEN_Pin;
  GPIO_InitStruct.Mode = GPIO_MODE_OUTPUT_OD;
  GPIO_InitStruct.Pull = GPIO_NOPULL;
  GPIO_InitStruct.Speed = GPIO_SPEED_FREQ_LOW;
  HAL_GPIO_Init(SolarEN_GPIO_Port, &GPIO_InitStruct);

  /*Configure GPIO pin : PH3 */
  GPIO_InitStruct.Pin = GPIO_PIN_3;
  GPIO_InitStruct.Mode = GPIO_MODE_ANALOG;
  GPIO_InitStruct.Pull = GPIO_NOPULL;
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
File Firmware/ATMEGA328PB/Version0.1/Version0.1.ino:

#include <avr/sleep.h>
#include <avr/wdt.h>
#include <Time.h>
#include <SPI.h>
#include <GxEPD2_3C.h>
#include <Fonts/FreeSansBold12pt7b.h>
#include <Fonts/FreeSans24pt7b.h>
//#include "Ublox.h"

//Time
volatile time_t unix = 1652459254;

//Display
const int pin_LCD_BUSY = 6; //PD6
const int pin_LCD_RES = 7; //PD7
const int pin_LCD_DC = 8; //PB0
const int pin_LCD_CS = 9; //PB1
#include "GxEPD2_display_selection_new_style.h"
const uint8_t dispDrawFast = 30;
const uint8_t dispDrawSlow = 300;
uint32_t dispNextDraw = 0;
uint8_t dispDrawSpeed = dispDrawFast; //State machine

//GPS
//Ublox myGPS(&Serial1);
const int pin_GPS_EN = 18; //PC4
const int pin_GPS_EXINT = 19; //PC5

//IO
const int pin_LED = 17; //PC3
const int pin_TEST = 2; //PD2

//Power
uint32_t VCAPmV;
uint16_t rawADC;
const long powerSTBY = 2400;
const long powerLOW = 2600;
const long powerHIGH = 3200;
const long powerWARN = 3450;

void LCDBusyCallback(const void* p) { //Needs to be established before use
  cpuSleep(SLEEP_MODE_IDLE);
}

void setup() {
  PRR0 = 0b10011000;//Shutdown TWI0, UART1, TIM1
  PRR1 = 0b00111101;//Shutdown TWI1, PTC, TIM4, SPI1, TIM3
  pinMode(pin_LED, OUTPUT);
  tim2Setup();
  //display.epd2.setBusyCallback(LCDBusyCallback);
  display.setTextWrap(false);
  display.init();
}

void loop() {
  powerMachine();
  drawPaper();
  //goToSleep();
}

void powerMachine() {
  //Read VCC, Change states and timers
  readVcc();

  //DISP
  if ((VCAPmV < powerSTBY) && (dispDrawSpeed != 0)) { //stop Disp
    dispDrawSpeed = 0;
  } else if ((VCAPmV < powerHIGH) && (dispDrawSpeed != dispDrawSlow)) { //Draw slow
    dispDrawSpeed = dispDrawSlow;
  } else if (dispDrawSpeed != dispDrawFast) { //Draw fast
    dispDrawSpeed = dispDrawFast;
  }

  //GPS

  //LED
  if (VCAPmV > powerWARN) {
    //Drain extra power with LED
    digitalWrite(pin_LED, HIGH);
  } else {
    digitalWrite(pin_LED, LOW);
  }
}

void tim2Setup() {
  //RESET
  ASSR = 0;
  TCNT2 = 0;
  TCCR2A = 0;
  TCCR2B = 0;
  //SETUP
  ASSR = (1 << AS2);//Enable asynchronous mode
  TCCR2A = (1 << WGM21); //Clear on compare
  TCCR2B = (1 << CS22) | (1 << CS21) | (1 << CS20); //set prescaler 32768/1024
  OCR2A = 32; //output compare value
  while ((ASSR & ((1 << OCR2AUB) | (1 << OCR2BUB) | (1 << TCR2AUB) | (1 << TCR2BUB) | (1 << TCN2UB)))) { //wait for registers update
    cpuSleep(SLEEP_MODE_IDLE);
  }
  TIFR2  = (1 << TOV2) | (1 << OCF2A) | (1 << OCF2B);//clear interrupt flags
  TIMSK2  = (1 << OCIE2A); //enable Output Compare A interrupt
}

void readVcc() {
  // Read 1.1V reference against AVcc
  ADCSRA = (1 << ADEN); //enable ADC
  ADCSRA |= (1 << ADPS2) | (1 << ADPS1) | (1 << ADPS0); //8MHZ DIV128 = 62.5kHZ
  ADMUX = (1 << REFS0) | (1 << MUX3) | (1 << MUX2) | (1 << MUX1);
  ADCSRA |= (1 << ADSC); // Convert
  while (bit_is_set(ADCSRA, ADSC));
  rawADC = ADCW; //toss this
  ADCSRA |= (1 << ADSC); // Convert
  while (bit_is_set(ADCSRA, ADSC));
  rawADC = ADCW;
  VCAPmV = rawADC;
  VCAPmV = 1126400 / VCAPmV; // Back-calculate AVcc in mV
  ADCSRA = 0; //disable ADC
}

void drawPaper() {
  if (dispDrawSpeed != 0 && dispNextDraw < unix) {
    display.setRotation(0); //Get from ACCEL
    display.setFullWindow();
    display.firstPage();
    do
    {
      display.fillScreen(GxEPD_WHITE);
      display.setFont(&FreeSansBold12pt7b);
      //Time
      display.setCursor(0, 20);
      display.print(getTimeString());

      //Battery
      display.setCursor(0, 41);
      display.print(VCAPmV);
      display.print(F("mV"));

      //Fix Sats
      display.setCursor(0, 62);
      display.print(F("SATS "));
      //display.print(myGPS.num_satellites());

      //Age
      display.setCursor(0, 84);
      display.print(F("AGE "));
      //display.print(unix - myGPS.UTC());
      display.print(F("S"));

      //Lat
      display.setFont(&FreeSans24pt7b);
      display.setCursor(0, 127);
      //display.print(abs(myGPS.lat_deg()), 3);
      display.print(F("N"));
      //Long
      display.setCursor(0, 163);
      //display.print(abs(myGPS.long_deg()), 3);
      display.print(F("W"));
      //ALT
      display.setCursor(0, 199);
      //display.print(myGPS.alt_m(), 1);
      display.print(F("m"));
    }
    while (display.nextPage());
    display.hibernate();
    dispNextDraw = unix + dispDrawSpeed;
  }
}

char* getTimeString() {
  struct tm *tmp = gmtime(&unix);
  static char buf[9];
  sprintf(buf, "%02d:%02d:%02d %02d/%02d", tmp->tm_hour, tmp->tm_min, tmp->tm_sec, tmp->tm_mday + 1, tmp->tm_mon + 1);
  return buf;
}

void goToSleep() {
  if (VCAPmV < powerWARN) {
    cpuSleep(SLEEP_MODE_PWR_SAVE);
  }
}

void cpuSleep(byte sleepMode) {
  set_sleep_mode(sleepMode);
  sleep_enable();
  sleep_mode();
  // Upon waking up, sketch continues from this point.
  sleep_disable();
}

void WDThandler() {
  /*Note on "Interrupt and System Reset Mode"
    The first timeout in the Watchdog Timer will set WDIF.
    Executing the corresponding interrupt vector will clear WDIE and WDIF automatically by hardware (the Watchdog goes to System Reset Mode).
    To stay in Interrupt and System Reset Mode, WDIE must be set after each interrupt.
  */
  cli();
  wdt_reset(); //reset so we dont trigger ISR by accident
  MCUSR = 0;
  WDTCSR |=  (1 << WDCE) | (1 << WDE); //Enable WDT changes
  WDTCSR  =  (1 << WDP0) | (1 << WDP3) | (1 << WDIE) | (1 << WDE); // 8.0 seconds with Interrupt and System Reset
  sei();
}

ISR(ADC_vect) {
  //when new ADC value ready
}

ISR(WDT_vect) {
  //Should go to top of loop and recheck
}

ISR(TIMER2_COMPA_vect) {
  unix++;
}

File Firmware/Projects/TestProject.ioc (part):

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Mcu.Name=STM32WB5MMGHx
Mcu.Package=LGA86
Mcu.UserName=STM32WB5MMGHx
PA4.GPIOParameters=GPIO_Label
PA4.GPIO_Label=SolarSense
PA4.Signal=ADCx_IN9
PA5.GPIOParameters=GPIO_Label
PA5.GPIO_Label=VBATSense
PA5.Signal=ADCx_IN10
PA6.GPIOParameters=GPIO_Label
PA6.GPIO_Label=VBATMIDSense
PA6.Signal=ADCx_IN11
PB2.Mode=WaveformGeneration
PB2.Signal=LPTIM1_OUT
PC5.GPIOParameters=GPIO_Label
PC5.GPIO_Label=LED1
PC5.Signal=GPIO_Output
RCC.HSE_VALUE=32000000
RCC.SYSCLKFreq_VALUE=32000000
RCC.SYSCLKSource=RCC_SYSCLKSOURCE_HSE
board=custom

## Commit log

2021-11-30 Initial Upload
2021-11-30 Revert "Update README.md"
    This reverts commit 456681cdc3c9041e490a714788badee7f2f253bc.
2021-11-30 Revert "Update README.md"
    This reverts commit b648ac10901cc942cb3e6df4b6ca93423926bfcd.
2021-11-30 Add details, Power Mode layout
2021-12-01 Update Power Modes
2021-12-01 Update PCB1.0 with new layout
    Reverse the LCD direction for more space on the GPS signal
2021-12-02 Cost reduction, remove second mppt
2021-12-02 Add list of cities
2021-12-02 Update BOM, start treebuilders
2021-12-03 Replace Antenna
2021-12-03 Redraw PCB1.0
2021-12-03 Update BOM
    Add 3.3pF
2021-12-03 Write some more
2021-12-03 Add a line
2021-12-06 Cost Reduction
2021-12-06 Most Cost Savings
2021-12-06 Add information sheets
2021-12-08 Mess with 3D
2021-12-10 Rebuild outputs for production sample
2021-12-13 Add more docs
2021-12-13 Revert "Merge branch 'main' of https://github.com/jacky4566/Veridian-Heliograph"
    This reverts commit 3d311697883c021d2cdad3487d82eaf0104020f1, reversing
    changes made to 2ae0f60846ad75c4f8cb230a5fde49ffea6f6208.
2021-12-13 Firmware resolve
2021-12-13 Add Demo Build project
2021-12-14 More Projects
2021-12-15 Learning
2021-12-22 Start GNSS Driver
2021-12-23 Tweak part numbers
2021-12-25 Add PCB1.1
2021-12-27 Add version 0.1
2021-12-28 Rename demo project
2021-12-28 Remove debug. add Gitignore
2021-12-28 Add ignore Debug/
2021-12-28 Add OTA
    First attempt for OTA
2021-12-28 Write some more stuff about this project.
2021-12-28 Add some GNSS ground work and IWDG 2s
2021-12-29 Add more GNSS stuff
2021-12-29 Add some experimental low power stuff for LPUART
2021-12-29 Add some SPI framework
2021-12-29 split out ADC SPI functions
2021-12-30 improve some code.
2021-12-31 Begin with stop mode
2021-12-31 Slower advertising, Better STOP2
2022-01-01 Add some display stuff.
2022-01-03 Add some disconnect code
2022-01-05 Add in some ubx configuration and LPUART transmit
2022-01-10 Add some rotate display stuff
2022-01-13 Change VCC to 2.87 Remove LCD connector
2022-01-13 Cost savings!
2022-01-20 tweak PCB1.1 add some notes
2022-01-20 Play with USB idea. Update to KiCad 5
2022-01-21 First crack at Andoid app
2022-01-21 Working Template 1
2022-01-21 Fuck it, single Activity for now
2022-01-25 Add more App, DropBLE
2022-01-25 Change solder mask
2022-01-25 Add some datasheets
2022-01-26 Remove control app
2022-02-01 Add custom library revise M4 mount
2022-02-01 Tweak PCB
2022-02-02 Revise
2022-02-02 Add V1.2 with UART fixes
2022-02-02 Tweak Grounding
2022-02-07 Rebuild PCB1.2 and submit for build
2022-03-03 PCBV1.2
2022-03-03 Move symbols to lib
2022-03-03 Drop MPPT buck for diode cost
2022-03-08 Change LCD
2022-04-09 Rework power system for hybrid cap and bq25770
2022-04-09 Tweak Epaper driver
2022-04-10 Fix Reverse Epaper Connector
2022-04-12 PCB1.4
2022-04-12 zips
2022-04-18 Update 1.4 BOM
2022-04-19 firmware stuff
2022-04-19 1.4 MEga328PB
2022-04-20 add tqfp footprint
2022-04-20 reduce power BOM
2022-04-28 Version 1.4
2022-05-11 tweak pcb1.5
2022-05-12 Add demo code
2022-05-14 Some dumb changes
2022-05-14 More Data
2022-05-16 Manufacture 1.5 PCB
2022-05-16 Firmwars
2022-05-17 Add DataSheets
2022-05-20 Work on LCD library
2022-05-20 More Lines
2022-05-20 More Code
2022-05-26 Add Dev Project
2022-05-28 Progress!
2022-05-30 ProgressMK2
2022-05-30 Remove Metadata
2022-05-30 Cleanup
2022-05-30 Start PCB1.6
2022-05-31 More Work
2022-05-31 First working Version
2022-06-01 Pre-nanoprintf
2022-06-01 More Progress
2022-06-03 Tweaking and Twerking
2022-06-03 More Tweaking
2022-06-03 small tweaks
2022-06-04 Replace GNSS with L96
2022-06-19 Update Ignore
2022-06-19 Working firmware
2022-06-19 Fix stashed changes
2022-08-06 Update PCBV10
2022-08-11 PCB1.6
2022-10-21 Adding tarfile member sanitization to extractall()
2022-11-03 Tweak 1.7
2022-11-03 Submit board 1.7
2022-11-23 Tweak UI and Voltages
2023-04-15 add USB!
2023-04-17 Add USB pulldown and SWO
2023-04-20 Do PCB 1.7
2023-04-26 Tweak Resistors
2023-05-10 v1.8
2023-05-10 More messing around
2023-05-11 workingcopy
2023-05-11 Tweak values
2023-05-15 Add GPS SLOW
2023-05-16 Add Power Save GNSS
